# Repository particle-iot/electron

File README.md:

# Electron

The Electron is a tiny cellular development kit based around U-Blox's SARA U-series (3G) or G-series (2G) cellular modem module and a STM32F205 ARM Cortex M3 microcontroller.

The Electron has a footprint which is a drop-in compatible with the Particle Photon or Core.

Compared to the Particle Photon, the Electron introduces additional hardware features and changes:

1. JST LiPo battery connector.
2. Switch-mode battery charge management and system power path management circuit.
3. Fuel gauge circuit for lithium batteries.
4. Nano-SIM connector.
5. Access to USB data lines. 
6. 12 additional GPIO Pins.
7. 4 additional ADC channels.
8. 6 Timer channels exposed.
9. 2 additional UART peripherals.
10. 1 additional SPI and CAN peripheral.

A detailed description of the pin mapping can be found in **electron-pinmap_v1** spreadsheet.
* Sheet 1: Overview of the Electron pin-out.
* Sheet 2: Overview of the Photon pin-out for comparison.

### Pin Descriptions:
- **VIN:** This is the power supply pin to the Electron with a voltage range of 3.6 to 5.5VDC (internally regulated down to 3.3VDC). When the Electron is powered via its USB port, this pin will *ouput* a voltage of approximately 4.7VDC. Why 4.7 and not 5? Well, the actual voltage will be the USB voltage, which is normally 5, minus the forward voltage drop (0.3V) of the protection diode.
- **RST:** This is an active-low reset pin for the Electron.
- **VBAT:** Supply to the internal RTC, backup registers and SRAM (1.8 to 3.3VDC).
- **3V3:** This pin is the output of the on-board regulator. When powering the Photon via VIN or the USB port, this pin will *output* a voltage of 3.3VDC.
- **WKP:** This is an active-high input that allows you to wakeup the module from sleep/deep sleep modes. When not used as a WAKEUP, this pin can also be used as a digital GPIO, ADC input or PWM.
- **A0 - A5:** These can be used as digital GPIOs, ADC inputs. Alternate functions include: SPI, PWM and DAC.
- **B0 - B5:** These can be used as digital GPIOs, partial ADC inputs, partial PWM outputs.
- **C0 - C5:** These can be used as digital GPIOs.
- **D0 - D7:** These can be used as digital GPIOs. Alternate functions include: UART, SPI, I2C, PWM and CAN. 
- **DAC:** This pin can be used as a digital GPIO, ADC input or as a DAC ouput.
- **RX:** Primarily used as UART RX, but can also be used as a digital GPIO, ADC input or PWM.
- **TX:** Primarily used as UART TX, but can also be used as a digital GPIO, ADC input or PWM.

Please review the pinmap spreadsheet to better understand the alternate functions of the GPIO pins.

### Eagle (schematic, pcb layout and drc):
**eagle** contains the history of Electron designs and **electron_v020** is the latest design.  The **libraries** folder contains the Eagle library for parts used on the Electron.

### License

Designed by Particle. Distributed under a Creative Commons Attribution, Share-Alike license.
Development kits based on this product should be distributed under a similar license.
Commercial products using the Electron as a reference design need not comply with this license; further questions can be sent to hello@particle.io.
Check license.txt for more information.

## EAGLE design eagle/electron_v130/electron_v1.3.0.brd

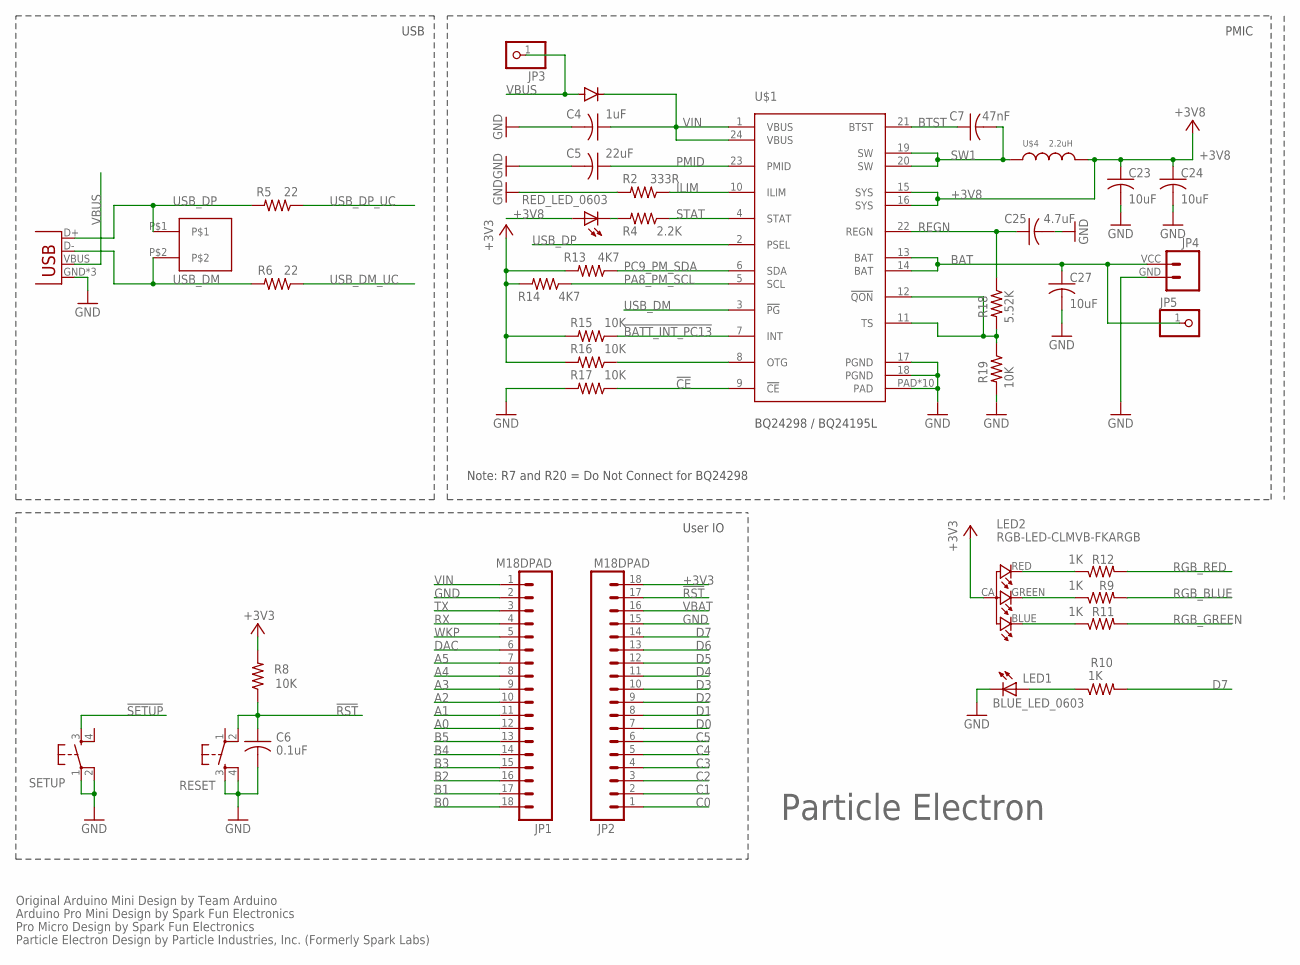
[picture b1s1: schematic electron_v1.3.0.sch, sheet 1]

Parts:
BLUE_LED_0603: LEDNOSILK; LED-0603-NS
C4: 1uF; C0603_B
C5: 22uF; C0603_B
C6: 0.1uF; C0402_B
C7: 47nF; C0402_B
C23, C24, C27: 10uF; C0603_B
C25: 4.7uF; C0603_B
JP1, JP2: M18DPAD; 1X18-D-PADS
JP3, JP5: PINHD-1X1NOSILK; 1X01_NO_SILK
JP4: M024UCON-15767; JST-2-SMD-VERT
LED2: RGB-LED-CLMVB-FKARGB; PLCC4-2MM-RGB
R2: 333R; R0402_B
R4: 2.2K; R0402_B
R5, R6: 22; R0402_B
R8, R15, R16, R17, R19: 10K; R0402_B
R9, R10, R11, R12: 1K; R0402_B
R13, R14: 4K7; R0402_B
R18: 5.52K; R0402_B
RED_LED_0603: LED0603; LED-0603
RESET: KMR211GLFS; TACTILE_SWITCH_SMD
SETUP: KMR211GLFS; TACTILE_SWITCH_SMD
U$1: BQ24298 / BQ24195L; QFN24
U$3: DIODE_NT; DIODE-DO-220AA_NT(SMP)
U$4: 2.2uH; INDUCTOR-4040
U$7: M02_0.05_HEADER
X1: USB-MICROB; USB-MICROB-SLOT-HOLE

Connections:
!BATT_INT_PC13: R15.1, U$1.7 (INT); also elsewhere on the board
!CE: R17.1, U$1.9 (!CE)
!RST: C6.1, JP2.17, R8.1, RESET.2; also elsewhere on the board
!SETUP: SETUP.3; also elsewhere on the board
+3V3: JP2.18, LED2.CA (1), R8.2, R13.2, R14.2, R15.2, R16.2; also elsewhere on the board
+3V8: C23.1, C24.1, RED_LED_0603.A, U$1.15 (SYS), U$1.16 (SYS), U$4.P$2 (2); also elsewhere on the board
A0: JP1.12; also elsewhere on the board
A1: JP1.11; also elsewhere on the board
A2: JP1.10; also elsewhere on the board
A3: JP1.9; also elsewhere on the board
A4: JP1.8; also elsewhere on the board
A5: JP1.7; also elsewhere on the board
B0: JP1.18; also elsewhere on the board
B1: JP1.17; also elsewhere on the board
B2: JP1.16; also elsewhere on the board
B3: JP1.15; also elsewhere on the board
B4: JP1.14; also elsewhere on the board
B5: JP1.13; also elsewhere on the board
BAT: C27.1, JP4.VCC (2), JP5.1, U$1.13 (BAT), U$1.14 (BAT); also elsewhere on the board
BTST: C7.1, U$1.21 (BTST)
C0: JP2.1; also elsewhere on the board
C1: JP2.2; also elsewhere on the board
C2: JP2.3; also elsewhere on the board
C3: JP2.4; also elsewhere on the board
C4: JP2.5; also elsewhere on the board
C5: JP2.6; also elsewhere on the board
D0: JP2.7; also elsewhere on the board
D1: JP2.8; also elsewhere on the board
D2: JP2.9; also elsewhere on the board
D3: JP2.10; also elsewhere on the board
D4: JP2.11; also elsewhere on the board
D5: JP2.12; also elsewhere on the board
D6: JP2.13; also elsewhere on the board
D7: JP2.14, R10.2; also elsewhere on the board
DAC: JP1.6; also elsewhere on the board
GND: BLUE_LED_0603.C, C4.2, C5.2, C6.2, C23.2, C24.2, C25.2, C27.2, JP1.2, JP2.15, JP4.GND (1), R2.2, R17.2, R19.2, RESET.3, RESET.4, SETUP.1, SETUP.2, U$1.17 (PGND), U$1.18 (PGND), U$1.PAD, U$1.PAD@1 (PAD), U$1.PAD@2 (PAD), U$1.PAD@3 (PAD), U$1.PAD@4 (PAD), U$1.PAD@5 (PAD), U$1.PAD@6 (PAD), U$1.PAD@7 (PAD), U$1.PAD@8 (PAD), U$1.PAD@9 (PAD), X1.GND, X1.MT1 (GND), X1.MT2 (GND); also elsewhere on the board
ILIM: R2.1, U$1.10 (ILIM)
LED1: BLUE_LED_0603.A, R10.1
unnamed: R4.2, RED_LED_0603.C
unnamed: R16.1, U$1.8 (OTG)
unnamed: LED2.BLUE (2), R11.1
unnamed: LED2.GREEN (3), R9.1
unnamed: LED2.RED (4), R12.1
PA8_PM_SCL: R14.1, U$1.5 (SCL); also elsewhere on the board
PC9_PM_SDA: R13.1, U$1.6 (SDA); also elsewhere on the board
PMID: C5.1, U$1.23 (PMID)
REGN: C25.1, R18.1, U$1.22 (REGN)
RGB_BLUE: R11.2; also elsewhere on the board
RGB_GREEN: R9.2; also elsewhere on the board
RGB_RED: R12.2; also elsewhere on the board
RX: JP1.4; also elsewhere on the board
STAT: R4.1, U$1.4 (STAT)
SW1: C7.2, U$1.19 (SW), U$1.20 (SW), U$4.P$1 (1)
TS: R18.2, R19.1, U$1.11 (TS), U$1.12 (!QON)
TX: JP1.3; also elsewhere on the board
USB_DM: R6.2, U$1.3 (!PG), U$7.P$2, X1.D-
USB_DM_UC: R6.1; also elsewhere on the board
USB_DP: R5.2, U$1.2 (PSEL), U$7.P$1, X1.D+
USB_DP_UC: R5.1; also elsewhere on the board
VBAT: JP2.16; also elsewhere on the board
VBUS: JP3.1, U$3.ANODE, X1.VBUS
VIN: C4.1, JP1.1, U$1.1 (VBUS), U$1.24 (VBUS), U$3.CATHODE
WKP: JP1.5; also elsewhere on the board

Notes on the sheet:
PMIC
User IO
USB
Particle Electron
Note: R7 and R20 = Do Not Connect for BQ24298
Original Arduino Mini Design by Team Arduino
Arduino Pro Mini Design by Spark Fun Electronics
Pro Micro Design by Spark Fun Electronics
Particle Electron Design by Particle Industries, Inc. (Formerly Spark Labs)

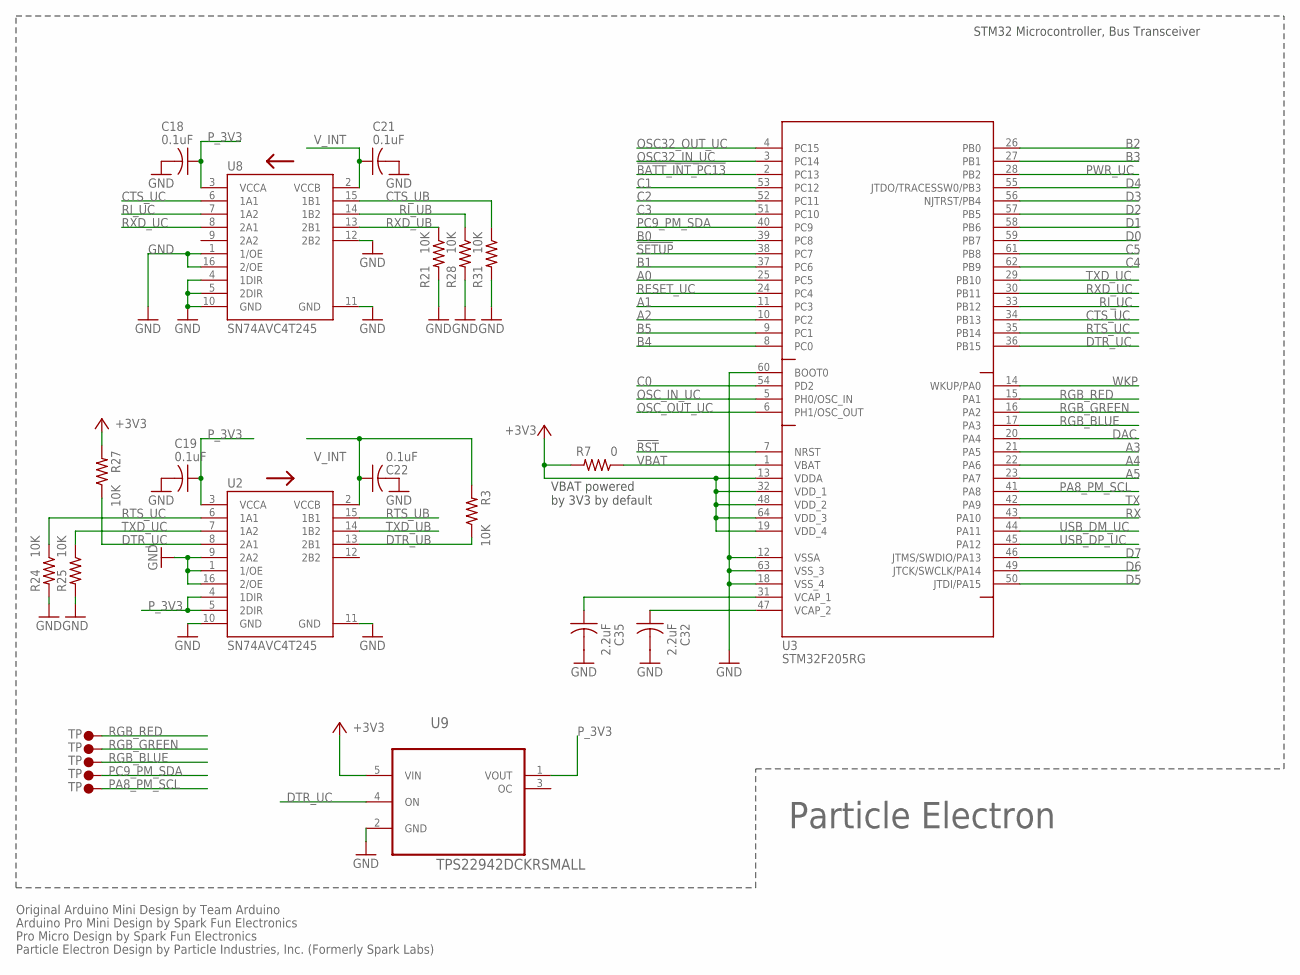
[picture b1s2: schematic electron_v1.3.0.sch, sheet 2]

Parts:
C18, C19, C21, C22: 0.1uF; C0402_B
C32, C35: 2.2uF; C0402_B
R3, R21, R24, R25, R27, R28, R31: 10K; R0402_B
R7: 0; R0402_B
U2, U8: SN74AVC4T245; UFQFN-16
U3: STM32F205RG; LQFP64
U9: TPS22942DCKRSMALL; SC70-5
U$8, U$9, U$11, U$12, U$13: TP0; TP30_BOT

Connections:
!BATT_INT_PC13: U3.2 (PC13); also elsewhere on the board
!RST: U3.7 (NRST); also elsewhere on the board
!SETUP: U3.38 (PC7); also elsewhere on the board
+3V3: R7.2, R27.2, U3.13 (VDDA), U3.19 (VDD_4), U3.32 (VDD_1), U3.48 (VDD_2), U3.64 (VDD_3), U9.5 (VIN); also elsewhere on the board
A0: U3.25 (PC5); also elsewhere on the board
A1: U3.11 (PC3); also elsewhere on the board
A2: U3.10 (PC2); also elsewhere on the board
A3: U3.21 (PA5); also elsewhere on the board
A4: U3.22 (PA6); also elsewhere on the board
A5: U3.23 (PA7); also elsewhere on the board
B0: U3.39 (PC8); also elsewhere on the board
B1: U3.37 (PC6); also elsewhere on the board
B2: U3.26 (PB0); also elsewhere on the board
B3: U3.27 (PB1); also elsewhere on the board
B4: U3.8 (PC0); also elsewhere on the board
B5: U3.9 (PC1); also elsewhere on the board
C0: U3.54 (PD2); also elsewhere on the board
C1: U3.53 (PC12); also elsewhere on the board
C2: U3.52 (PC11); also elsewhere on the board
C3: U3.51 (PC10); also elsewhere on the board
C4: U3.62 (PB9); also elsewhere on the board
C5: U3.61 (PB8); also elsewhere on the board
CTS_UB: R31.1, U8.15 (1B1); also elsewhere on the board
CTS_UC: U3.34 (PB13), U8.6 (1A1)
D0: U3.59 (PB7); also elsewhere on the board
D1: U3.58 (PB6); also elsewhere on the board
D2: U3.57 (PB5); also elsewhere on the board
D3: U3.56 (NJTRST/PB4); also elsewhere on the board
D4: U3.55 (JTDO/TRACESSW0/PB3); also elsewhere on the board
D5: U3.50 (JTDI/PA15); also elsewhere on the board
D6: U3.49 (JTCK/SWCLK/PA14); also elsewhere on the board
D7: U3.46 (JTMS/SWDIO/PA13); also elsewhere on the board
DAC: U3.20 (PA4); also elsewhere on the board
DTR_UB: R3.1, U2.13 (2B1); also elsewhere on the board
DTR_UC: R27.1, U2.8 (2A1), U3.36 (PB15), U9.4 (ON)
GND: C18.2, C19.2, C21.2, C22.2, C32.2, C35.2, R21.2, R24.2, R25.2, R28.2, R31.2, U2.1 (1/OE), U2.9 (2A2), U2.10 (GND), U2.11 (GND), U2.16 (2/OE), U3.12 (VSSA), U3.18 (VSS_4), U3.60 (BOOT0), U3.63 (VSS_3), U8.1 (1/OE), U8.4 (1DIR), U8.5 (2DIR), U8.10 (GND), U8.11 (GND), U8.12 (2B2), U8.16 (2/OE), U9.2 (GND); also elsewhere on the board
unnamed: C35.1, U3.31 (VCAP_1)
unnamed: C32.1, U3.47 (VCAP_2)
OSC32_IN_UC: U3.3 (PC14); also elsewhere on the board
OSC32_OUT_UC: U3.4 (PC15); also elsewhere on the board
OSC_IN_UC: U3.5 (PH0/OSC_IN); also elsewhere on the board
OSC_OUT_UC: U3.6 (PH1/OSC_OUT); also elsewhere on the board
PA8_PM_SCL: U3.41 (PA8), U$9.P$1; also elsewhere on the board
PC9_PM_SDA: U3.40 (PC9), U$8.P$1; also elsewhere on the board
PWR_UC: U3.28 (PB2); also elsewhere on the board
P_3V3: C18.1, C19.1, U2.3 (VCCA), U2.4 (1DIR), U2.5 (2DIR), U8.3 (VCCA), U9.1 (VOUT)
RESET_UC: U3.24 (PC4); also elsewhere on the board
RGB_BLUE: U3.17 (PA3), U$13.P$1; also elsewhere on the board
RGB_GREEN: U3.16 (PA2), U$12.P$1; also elsewhere on the board
RGB_RED: U3.15 (PA1), U$11.P$1; also elsewhere on the board
RI_UB: R28.1, U8.14 (1B2); also elsewhere on the board
RI_UC: U3.33 (PB12), U8.7 (1A2)
RTS_UB: U2.15 (1B1); also elsewhere on the board
RTS_UC: R24.1, U2.6 (1A1), U3.35 (PB14)
RX: U3.43 (PA10); also elsewhere on the board
RXD_UB: R21.1, U8.13 (2B1); also elsewhere on the board
RXD_UC: U3.30 (PB11), U8.8 (2A1)
TX: U3.42 (PA9); also elsewhere on the board
TXD_UB: U2.14 (1B2); also elsewhere on the board
TXD_UC: R25.1, U2.7 (1A2), U3.29 (PB10)
USB_DM_UC: U3.44 (PA11); also elsewhere on the board
USB_DP_UC: U3.45 (PA12); also elsewhere on the board
VBAT: R7.1, U3.1 (VBAT); also elsewhere on the board
V_INT: C21.1, C22.1, R3.2, U2.2 (VCCB), U8.2 (VCCB); also elsewhere on the board
WKP: U3.14 (WKUP/PA0); also elsewhere on the board

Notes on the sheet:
Particle Electron
STM32 Microcontroller, Bus Transceiver
Original Arduino Mini Design by Team Arduino
Arduino Pro Mini Design by Spark Fun Electronics
Pro Micro Design by Spark Fun Electronics
Particle Electron Design by Particle Industries, Inc. (Formerly Spark Labs)
VBAT powered by 3V3 by default

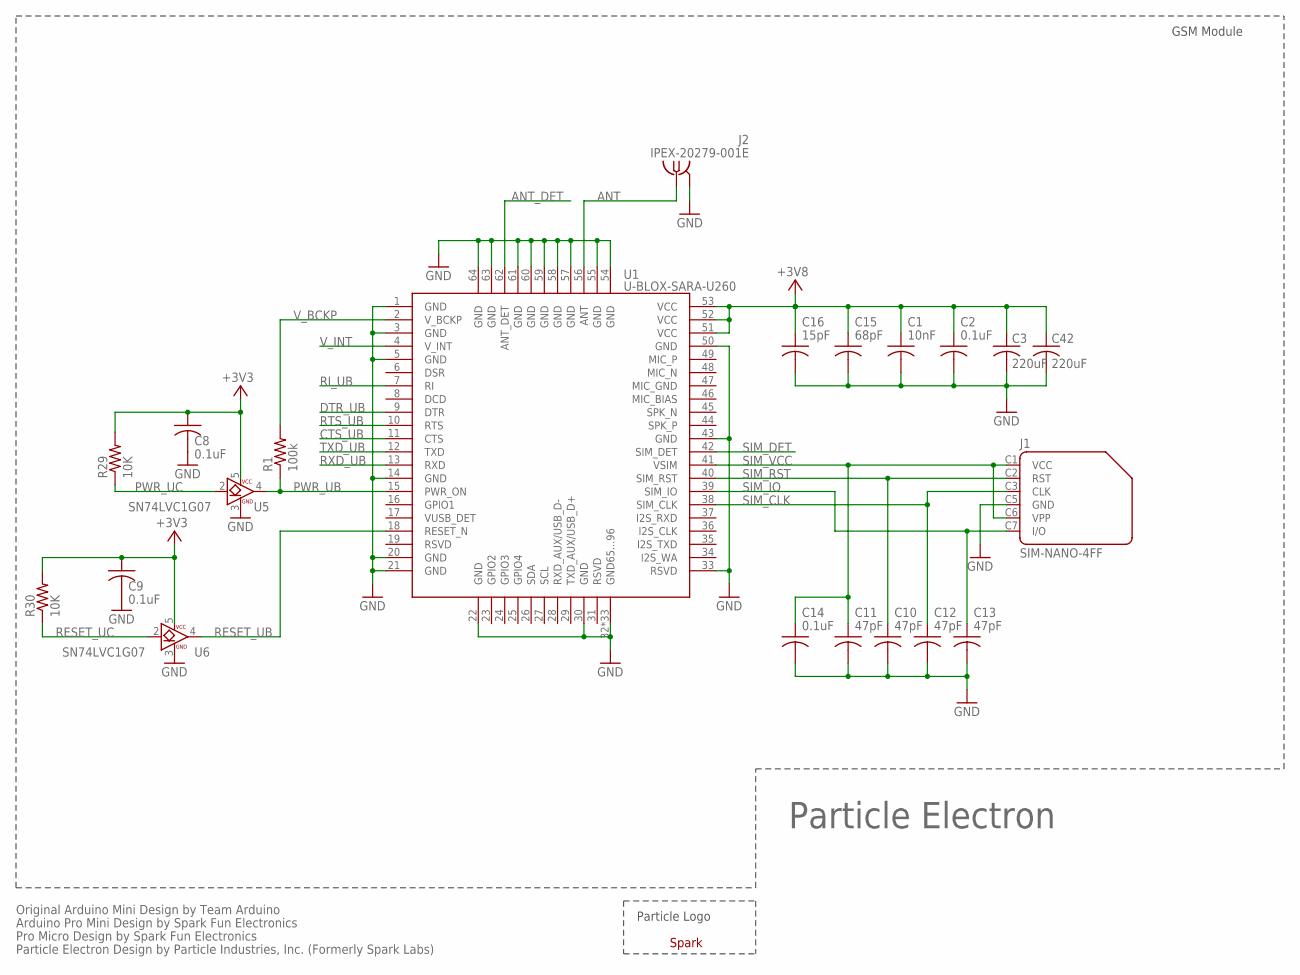
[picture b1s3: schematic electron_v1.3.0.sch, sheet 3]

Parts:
C1: 10nF; C0402_B
C2, C8, C9, C14: 0.1uF; C0402_B
C3, C42: 220uF; C1210
C10, C11, C12, C13: 47pF; C0402_B
C15: 68pF; C0402_B
C16: 15pF; C0402_B
J1: SIM-NANO-4FF; GCT-SIM8100
J2: IPEX-20279-001E
R1: 100k; R0402_B
R29, R30: 10K; R0402_B
U1: U-BLOX-SARA-U260; U-BLOX-SARA-U2
U5, U6: SN74LVC1G07; SC-70-5
U$2: SPARK_LOGO2

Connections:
+3V3: C8.1, C9.1, R29.2, R30.2, U5.5 (VCC), U6.5 (VCC); also elsewhere on the board
+3V8: C1.1, C2.1, C3.1, C15.1, C16.1, C42.1, U1.51 (VCC), U1.52 (VCC), U1.53 (VCC); also elsewhere on the board
ANT: J2.1, U1.56 (ANT)
ANT_DET: U1.62 (ANT_DET)
CTS_UB: U1.11 (CTS); also elsewhere on the board
DTR_UB: U1.9 (DTR); also elsewhere on the board
GND: C1.2, C2.2, C3.2, C8.2, C9.2, C10.2, C11.2, C12.2, C13.2, C14.2, C15.2, C16.2, C42.2, J1.C5 (GND), J2.2@1 (GND), J2.2@2 (GND), U1.1 (GND), U1.3 (GND), U1.5 (GND), U1.14 (GND), U1.20 (GND), U1.21 (GND), U1.22 (GND), U1.30 (GND), U1.32 (GND65...96), U1.33 (RSVD), U1.43 (GND), U1.50 (GND), U1.54 (GND), U1.55 (GND), U1.57 (GND), U1.58 (GND), U1.59 (GND), U1.60 (GND), U1.61 (GND), U1.63 (GND), U1.64 (GND), U1.65 (GND65...96), U1.66 (GND65...96), U1.67 (GND65...96), U1.68 (GND65...96), U1.69 (GND65...96), U1.70 (GND65...96), U1.71 (GND65...96), U1.72 (GND65...96), U1.73 (GND65...96), U1.74 (GND65...96), U1.75 (GND65...96), U1.76 (GND65...96), U1.77 (GND65...96), U1.78 (GND65...96), U1.79 (GND65...96), U1.80 (GND65...96), U1.81 (GND65...96), U1.82 (GND65...96), U1.83 (GND65...96), U1.84 (GND65...96), U1.85 (GND65...96), U1.86 (GND65...96), U1.87 (GND65...96), U1.88 (GND65...96), U1.89 (GND65...96), U1.90 (GND65...96), U1.91 (GND65...96), U1.92 (GND65...96), U1.93 (GND65...96), U1.94 (GND65...96), U1.95 (GND65...96), U1.96 (GND65...96), U5.3 (GND), U6.3 (GND); also elsewhere on the board
PWR_UB: R1.1, U1.15 (PWR_ON), U5.4 (B)
PWR_UC: R29.1, U5.2 (A); also elsewhere on the board
RESET_UB: U1.18 (RESET_N), U6.4 (B)
RESET_UC: R30.1, U6.2 (A); also elsewhere on the board
RI_UB: U1.7 (RI); also elsewhere on the board
RTS_UB: U1.10 (RTS); also elsewhere on the board
RXD_UB: U1.13 (RXD); also elsewhere on the board
SIM_CLK: C12.1, J1.C3 (CLK), U1.38 (SIM_CLK)
SIM_DET: U1.42 (SIM_DET)
SIM_IO: C13.1, J1.C7 (I/O), U1.39 (SIM_IO)
SIM_RST: C10.1, J1.C2 (RST), U1.40 (SIM_RST)
SIM_VCC: C11.1, C14.1, J1.C1 (VCC), J1.C6 (VPP), U1.41 (VSIM)
TXD_UB: U1.12 (TXD); also elsewhere on the board
V_BCKP: R1.2, U1.2 (V_BCKP)
V_INT: U1.4 (V_INT); also elsewhere on the board

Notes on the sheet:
Particle Electron
GSM Module
Particle Logo
Original Arduino Mini Design by Team Arduino
Arduino Pro Mini Design by Spark Fun Electronics
Pro Micro Design by Spark Fun Electronics
Particle Electron Design by Particle Industries, Inc. (Formerly Spark Labs)

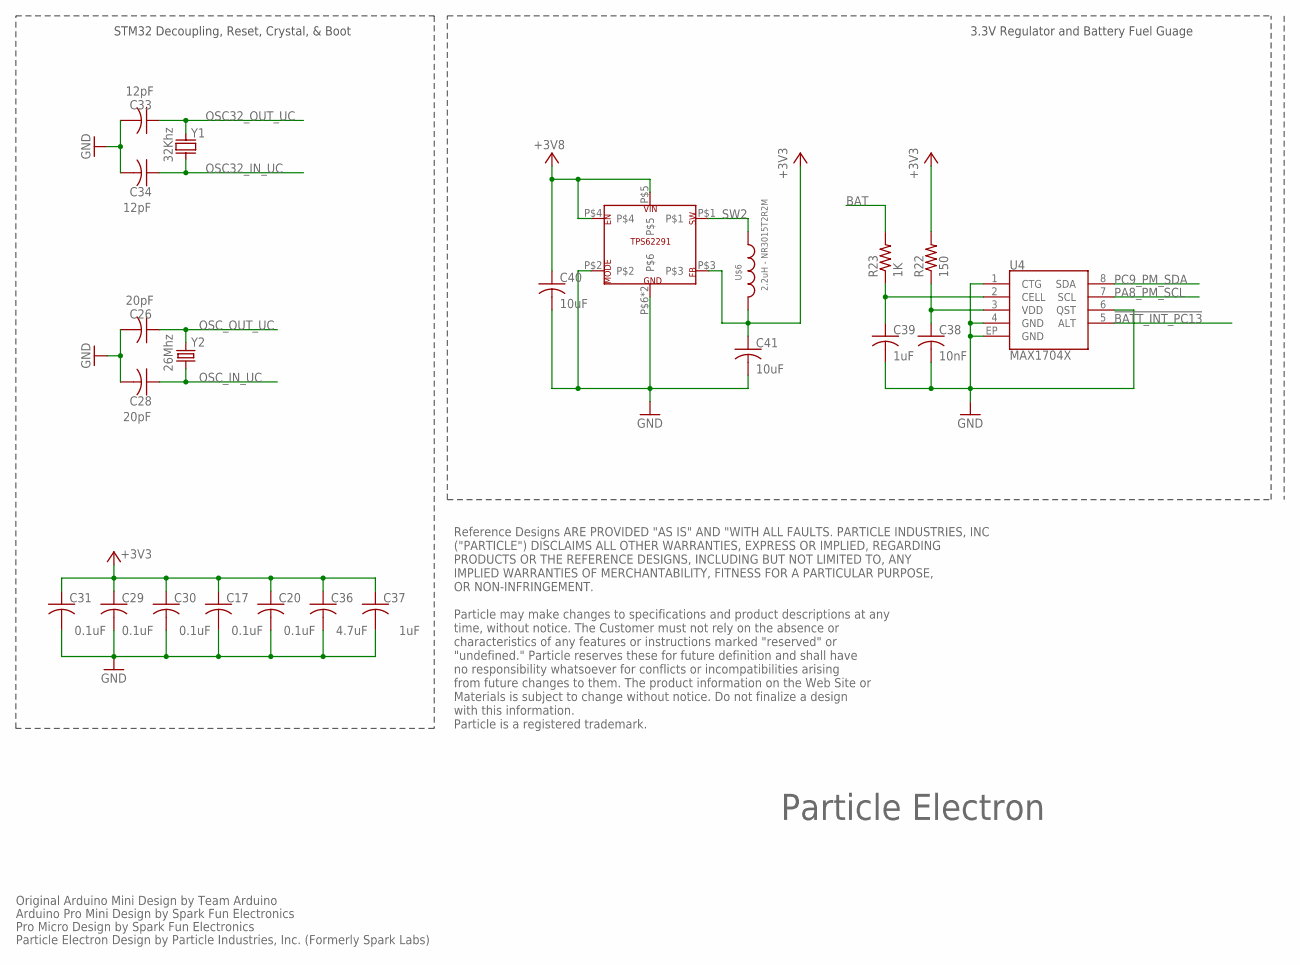
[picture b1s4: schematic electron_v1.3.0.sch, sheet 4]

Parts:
C17, C20, C29, C30, C31: 0.1uF; C0402_B
C26, C28: 20pF; C0402_B
C33, C34: 12pF; C0402_B
C36: 4.7uF; C0402_B
C37, C39: 1uF; C0402_B
C38: 10nF; C0402_B
C40, C41: 10uF; C0603_B
R22: 150; 0603-RES
R23: 1K; 0603-RES
U4: MAX1704X; TDFN-8
U$5: TPS62291DRV; S-PWSON-N6
U$6: 2.2uH - NR3015T2R2M; INDUCTOR-NR3015
Y1: 32Khz; FC135
Y2: 26Mhz; CRYSTAL-SMD-5X3

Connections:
!BATT_INT_PC13: U4.5 (ALT); also elsewhere on the board
+3V3: C17.1, C20.1, C29.1, C30.1, C31.1, C36.1, C37.1, C41.1, R22.2, U$5.P$3, U$6.2; also elsewhere on the board
+3V8: C40.1, U$5.P$4, U$5.P$5; also elsewhere on the board
BAT: R23.2; also elsewhere on the board
GND: C17.2, C20.2, C26.2, C28.2, C29.2, C30.2, C31.2, C33.2, C34.2, C36.2, C37.2, C38.2, C39.2, C40.2, C41.2, U4.1 (CTG), U4.4 (GND), U4.6 (QST), U4.EP (GND), U$5.P$2, U$5.P$6, U$5.TP; also elsewhere on the board
unnamed: C39.1, R23.1, U4.2 (CELL)
unnamed: C38.1, R22.1, U4.3 (VDD)
OSC32_IN_UC: C34.1, Y1.X1 (1); also elsewhere on the board
OSC32_OUT_UC: C33.1, Y1.X2 (2); also elsewhere on the board
OSC_IN_UC: C28.1, Y2.1; also elsewhere on the board
OSC_OUT_UC: C26.1, Y2.3 (2); also elsewhere on the board
PA8_PM_SCL: U4.7 (SCL); also elsewhere on the board
PC9_PM_SDA: U4.8 (SDA); also elsewhere on the board
SW2: U$5.P$1, U$6.1

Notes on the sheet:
Particle Electron
STM32 Decoupling, Reset, Crystal, & Boot
3.3V Regulator and Battery Fuel Guage
Original Arduino Mini Design by Team Arduino
Arduino Pro Mini Design by Spark Fun Electronics
Pro Micro Design by Spark Fun Electronics
Particle Electron Design by Particle Industries, Inc. (Formerly Spark Labs)
Reference Designs ARE PROVIDED "AS IS" AND "WITH ALL FAULTS. PARTICLE INDUSTRIES, INC ("PARTICLE") DISCLAIMS ALL OTHER WARRANTIES, EXPRESS OR IMPLIED, REGARDING PRODUCTS OR THE REFERENCE DESIGNS, INCLUDING BUT NOT LIMITED TO, ANY IMPLIED WARRANTIES OF MERCHANTABILITY, FITNESS FOR A PARTICULAR PURPO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

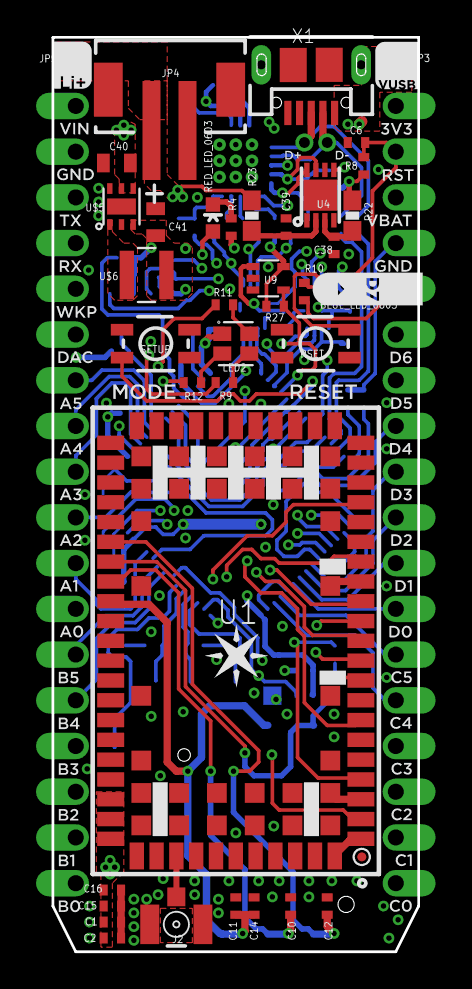
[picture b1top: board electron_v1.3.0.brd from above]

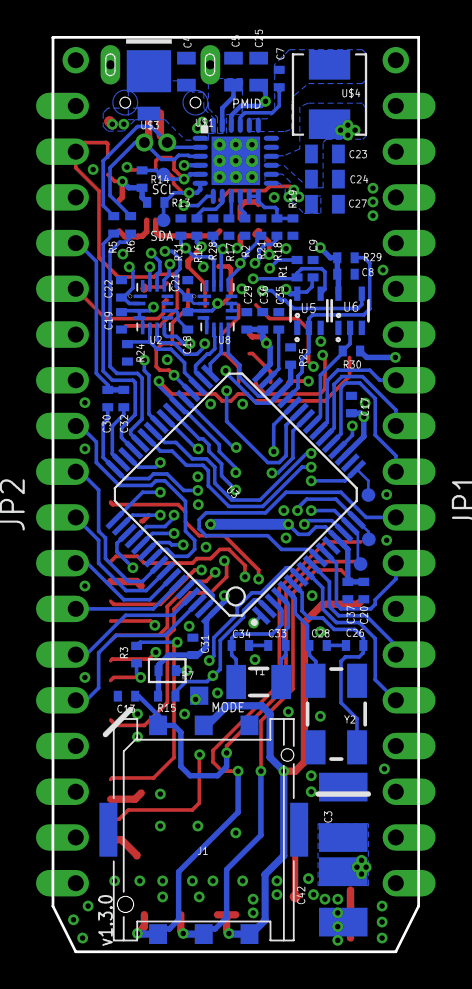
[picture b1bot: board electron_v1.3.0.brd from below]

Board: 4 copper layers, 20.3 x 50.8 mm, 106 parts (62 on the bottom side), 96 nets.

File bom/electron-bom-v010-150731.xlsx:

| NAME | PARTICLE ELECTRON
 | IDENTIFIER | DESCRIPTION | VALUE | V | A | W | TOL | PACKAGE ID | DESIGNATOR | QTY | MANUFACTURER | MANUFACTURER P/N
 | ACCESSORY | Mini Breadboard, White, 400pt tie point, 3.5 x 4.5cm |  |  |  |  |  | 3.5 x 4.5cm | ACC1 | 1 | Ningbo Everest | N/A
 | ACCESSORY | USB Micro-B Cable, 0.5m, White with Molded Logo |  |  |  |  |  | USB Micro-B, 0.5m | ACC2 | 1 | HOP Electronics | N/A
 | ACCESSORY | Li-Po Battery with JST Connector (2.0mm spacing, 2 pin), 3.7V, 2000mAh |  |  |  |  |  | 51mm x 34mm x 11.3mm | BAT1 | 1 | PKCell | LIPO 103450 2000mAh 3.7V
 | ANTENNA | Antenna - Penta band 850/900/1800/1900/2100 MHz |  |  |  |  |  | IPEX MHFI (U.FL) | ANT1 | 1 | Taoglas Taoglas Fei Yu Xin | PC104.07.0165C FXP14.07.0100A IPEX-PCB-113-L42
 | CAPACITOR | Ceramic Capacitor | 0.1uF | 6.3V |  |  | 0.1 | 0402 | C14, C17, C18, C19, C2, C20, C21, C22, C29, C30, C31, C6, C8, C9 | 14
 | CAPACITOR | Ceramic Capacitor | 10nF | 6.3V |  |  | 0.1 | 0402 | C1, C38 | 2
 | CAPACITOR | Ceramic Capacitor, X5R, Low ESR (<70 mΩ) | 10uF | 6.3V |  |  | 0.1 | 0603 | C23, C24, C27 | 3
 | CAPACITOR | Ceramic Capacitor | 12pF | 6.3V |  |  | 0.1 | 0402 | C33, C34 | 2
 | CAPACITOR | Ceramic Capacitor | 15pF | 6.3V |  |  | 0.1 | 0402 | C16 | 1
 | CAPACITOR | Ceramic Capacitor | 1uF | 6.3V |  |  | 0.1 | 0402 | C37, C39 | 3
 | CAPACITOR | Ceramic Capacitor, X5R, Low ESR (<70 mΩ) | 1uF | ≥25V |  |  | 0.1 | 0603 | C4 | 3
 | CAPACITOR | Ceramic Capacitor, X5R, Low ESR (<70 mΩ) | 2.2uF | 6.3V |  |  | 0.1 | 0402 | C32, C35 | 4
 | CAPACITOR | Ceramic Capacitor, X5R, Low ESR (<70 mΩ) | 2.2uF | 6.3V |  |  | 0.1 | 0603 | C40, C41 | 4
 | CAPACITOR | Ceramic Capacitor | 20pF | 6.3V |  |  | 0.1 | 0402 | C26, C28 | 2
 | CAPACITOR | Ceramic Capacitor, X5R, Low ESR (<70 mΩ) | 20uF | 6.3V |  |  | 0.1 | 0603 | C5 | 1
 | CAPACITOR | Tantalum Capacitor | 220uF | 6.3V |  |  | 0.1 | 2312 (6032 metric) | C3 | 1
 | CAPACITOR | Ceramic Capacitor, X5R, Low ESR (<70 mΩ) | 4.7uF | 6.3V |  |  | 0.1 | 0402 | C36 | 2
 | CAPACITOR | Ceramic Capacitor, X5R, Low ESR (<70 mΩ) | 4.7uF | 6.3V |  |  | 0.1 | 0603 | C25 | 2
 | CAPACITOR | Ceramic Capacitor | 47nF | 6.3V |  |  | 0.1 | 0402 | C7 | 1
 | CAPACITOR | Ceramic Capacitor | 47pF | 6.3V |  |  | 0.1 | 0402 | C10, C11, C12, C13 | 4
 | CAPACITOR | Ceramic Capacitor | 68pF | 6.3V |  |  | 0.1 | 0402 | C15 | 1
 | CONNECTOR | JST Connector | 2-pin |  |  |  |  | SMD, 2-pin, Vertical | JP4 | 1 | Kaweei | CW2001-02G-M01-D
 | CONNECTOR | Male Header (0.05" pitch) x 2 pins | 1x2 |  |  |  |  | 1x2, 0.05" pitch | U$7 | 1 | Kaweei
 | CONNECTOR | Male Header (0.1" pitch) x 18 pins | 1x18 |  |  |  |  | 1x18, 0.1" pitch | JP1, JP2 | 2 | Kaweei
 | CONNECTOR | USB Micro Connector with Slots, SMD |  |  |  |  |  | USB-MICROB-SLOT-HOLE | X1 | 1 | Kaweei | CMCUSB-5BFM2G-01-D
 | CONNECTOR | uFL Connector, IPEX-20279-001E, SMD |  |  |  |  |  | SMD | J2 | 1 | Kaweei | P1163-0140R
 | CONNECTOR | Nano SIM Card Slot |  |  |  |  |  | 10mm x 12.3mm | J1 | 1 | Kaweei | CSIM2545-06S-X
 | CRYSTAL | 26MHz, 18pF Load Capacitance, SMD5032, 4 pad | 26MHz |  |  |  | <±20ppm | 4-SMD, 5.0 x 3.2mm | Y2 | 1 | Song Ji | SJSMD5026M00018F20
 | CRYSTAL | 32.768KHz, 12.5pF Load Capacitance, SMD3215, 2 pad | 32.768KHz |  |  |  | <±20ppm | 2-SMD, 1.5 x 3.2mm | Y1 | 1 | Song Ji | SJ FC1332K012F520P
 | DIODE | Schottky Diode |  | 30V | 3A |  |  | DO-220AA | U$3 | 1 | Vishay | SS3P3-M3/84A
 | IC | Buffer |  |  |  |  |  | SC-70-5 | U5, U6 | 2 | Texas Instruments | SN74LVC1G07DCKR
 | IC | IC 2-Wire Fuel Gauge |  |  |  |  |  | TDFN-8 | U4 | 1 | Maxim | MAX17043G+T
 | IC | GSM Module |  |  |  |  |  | 16 x 26 x 3mm | U1 | 1 | u-blox | SARA-G350 SARA-U260 SARA-U270
 | IC | IC Bus Transceiver |  |  |  |  |  | 16-UQFN | U2, U8 | 2 | Texas Instruments | SN74AVC4T245RSVR
 | IC | Microcontroller |  |  |  |  |  | LQFP64 | U3 | 1 | ST Microelectronics | STM32F205RGT6TR
 | IC | Power Management IC (PMIC) |  |  |  |  |  | 24VQFN | U$1 | 1 | Texas Instruments | BQ24195RGER
 | IC | Voltage Regulator |  |  |  |  |  | 6-DSGBA | U$5 | 1 | Texas Instruments | LM3281YFQR
 | INDUCTOR | Ferrite Core Power Inductor (for 3V3 Regulator) | 0.47uH |  | 2.65A 2A |  |  | 2.5mm x 2.0mm 2.0mm x 2.0mm | U$6 | 1 | Abracon (preferred) TDK (backup) | ASPI-2510-R47N-T2 VLS2012ET-R47N
 | INDUCTOR | Power Inductor (for PMIC) | 2.2uH |  | 5A 3.7A |  |  | 5.0mm x 5.0mm x 4.5mm 4.9mm x 4.9mm x 4.1mm | U$4 | 1 | TDK (preferred) Taiyo Yuden (backup) | VLC5045T-2R2N NRS5040T2R2NMGJV
 | LED | Blue, SMD | Blue |  |  |  |  | 0603 | LED1 | 1 | Everlight | 19-217/BHC-ZL1M2RY/3T
 | LED | Red, SMD | Red |  |  |  |  | 0603 | LED3 | 1 | Everlight | 19-217/R6C-AL1M2VY/3T
 | LED | LED RGB, SMD | RGB |  |  |  |  | 4-PLCC (3.2 mm x 2.8mm) | LED2 | 1 | Cree | CLMVB-FKA-CFHEHLCBB7A363
 | PACKAGING | Static bag |  |  |  |  |  | TBD | PKG1 | 1
 | PACKAGING | Bubble bag |  |  |  |  |  | TBD | PKG2 | 1
 | PCB | FR4 4-Layer Photon PCB, 2-sided, matte black soldermask, cyan silkscreen |  |  |  |  |  | 20 mm x 50 mm | PCB1 | 1 | Truly
 | RESISTOR | Resistor | 0R |  |  | 1/10W | 0.05 | 0402 | R20, R7 | 2
 | RESISTOR | Resistor | 100k |  |  | 1/10W | 0.05 | 0402 | R1 | 1
 | RESISTOR | Resistor | 10K |  |  | 1/10W | 0.05 | 0402 | R13, R14, R15, R16, R17, R19, R8 | 7
 | RESISTOR | Resistor | 150R |  |  | 1/4W | 0.01 | 0603 | R22 | 1
 | RESISTOR | Resistor | 1K |  |  | 1/10W | 0.05 | 0603 | R23 | 1
 | RESISTOR | Resistor | 1K |  |  | 1/10W | 0.05 | 0402 | R10, R11, R12, R9 | 5
 | RESISTOR | Resistor | 2.2K |  |  | 1/10W | 0.05 | 0402 | R4 | 1
 | RESISTOR | Resistor | 22R |  |  | 1/10W | 0.01 | 0402 | R5, R6 | 2
 | RESISTOR | Resistor | 333R |  |  | 1/10W | 0.01 | 0402 | R2 | 1
 | RESISTOR | Resistor | 4K7 |  |  | 1/10W | 0.05 | 0402 | R21, R3 | 2
 | RESISTOR | Resistor | 5.52K |  |  | 1/10W | 0.01 | 0402 | R18 | 1
 | SIM | Nano SIM Card |  |  |  |  |  | Nano SIM | SIM1 | 1 | Telefonia | N/A
 | STICKER | UPC Sticker for the Electron |  |  |  |  |  | 40 mm x 20 mm | STK2 | 1 | Mei Ya | G350 (2G) - 724131462277 U260 (3G N.A.) - 724131462284 U270 (3G World) - 724131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
 | STICKER | "STICK-VINYL-2IN" sticker, 2", Circular, PVC - 5cm |  |  |  |  |  | Circular 2" | STK1 | 1 | Mei Ya
 | STICKER | Unique Barcode Sticker (DYMO 30346) |  |  |  |  |  | 1/2" x 1-7/8" | STK3 | 1 | Spark
 | SWITCH | Tactile Switch, Black Button | 160gF |  |  |  |  | 3.6mm x 3.1mm | MODE, RESET | 2 | Haoyu | TS-1185A-C

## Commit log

2015-07-29 Added 'Particle.lbr' Eagle Library
2015-07-29 Added .gitignore to ignore Eagle backup files
2015-07-29 Added Particle DRC and CAM files
2015-07-29 Added latest 'electron_v009' Eagle design folder/files (PCB Ver: 009)
2015-07-29 Added Manufacturing Gerber files for 'electron_v009'
2015-07-29 Added 'electron_v010' with improved RF layout & additional GND Vias
2015-07-29 updated readme wording
2015-07-29 Adding a BOM for v010
    Adding a BOM for the most current version of the Electron
2015-07-29 BOM tweaks v010
2015-07-29 BOM Tweaks again
2015-07-30 #8 Updated 3.3V regulator's inductor package footprint
2015-07-30 #7 Changed Button labels to SETUP and RESET
2015-07-30 #4 USB 5V exposed via hexagonal pad on top right corner above 3V3 pin
2015-07-30 #5 Added header pin labels that are not obscured by the u-blox module
2015-07-30 #1 Added u-blox positioning silkscreen
2015-07-30 Changed Particle IO to Particle
2015-07-30 added 18 pin header library part
2015-07-30 Added D pad footprint for Electron headers
    Device: M18
    Footprint: 1X18-D-PADS
2015-07-30 Added square long pad footprint for the Electron headers
    Device: M18
    Footprint: 1X18-SQR-LONG-PADS
2015-07-31 added 4020 type footprint to inductor device
    Device: Inductor
    Package: 4020TYPE
2015-07-31 #2 Replaced M18 round header pads with D-shaped pads and re-routed
2015-07-31 #10 ANT trace width @ RF net rules & deleted IPEX polygon cutouts
2015-07-31 #9 Added cutout on top layer under the ANT connector
2015-07-31 #13 Added more GND Vias around ANT connector and updated trace routes
2015-07-31 #11 Additional Vias added for battery trace connections
2015-07-31 Updated particle.lbr - Added a 4020 type inductor with bigger pads
2015-07-31 #12 Updated to bigger pads PMIC inductor footprint and power polygons
2015-07-31 Updated 5V header pad to round with drill size same as other headers
2015-07-31 Added more Vias on u-blox 3.8V trace connection (PCB Ver: 010 Ready)
2015-07-31 #15 Added Manufacturing Gerber files for 'electron_v010'
2015-07-31 Updated Top Silkscreen
2015-07-31 Updated Gerbers for PCB Ver 010
2015-07-31 added pin labels, thickened the text and moved particle logo
2015-07-31 generated new gerber files after adding pin labels
2015-07-31 Added specs for passives, some dottiest
    Check it out, yo
2015-08-01 Added some mfg documents for spinning up beta boards
    Added fab specs, 50 ohm impedance calcs, rf net PDF, and layer stackup
    explanation
2015-08-01 removed redundant gerber files
2015-08-03 Added electron_v010_schematic.pdf
2015-08-03 Added electron_v010_pcb-gerbers.pdf
2015-08-03 Updated Inductors in the BOM
    Hey Mohit!
2015-08-05 Added 'electron_v011' Eagle design folder/files (Work in Progress)
2015-08-05 BOM updated with passive values, some packaging stuff
    See the changelogzorzzzz :-)
2015-08-05 Manufacturing documents for the beta trials
2015-08-07 Updated BOM (C5 value from 20uF to 22uF)
2015-08-12 Updated BOM
    changed the quantity field of some passive components to match the
    correct number of designators.
2015-08-19 Added TPS62291 datasheet
2015-08-19 Created TPS62291DRV part in Particle library
2015-08-19 Replaced LM3281 with TPS62291 in schematic and updated circuit
2015-08-19 2.2uH inductor reused for 3.3V circuit, components placed and locked
2015-08-19 Completed v011 PCB routing for revised 3.3V power circuit #19
2015-08-19 Header pin labels updated #16
2015-08-19 Added orientation indicators to the silkscreen layers #17
2015-08-19 Added Manufacturing Gerber files for 'electron_v011'
2015-08-20 Updated BOM
    New voltage regulator, new power inductor, cross parts for passives.
2015-08-21 Added 'electron_v012' files-changed 3V3 power inductor footprint #21
2015-08-21 Minor silkscreen tweaks
2015-08-21 Added Manufacturing Gerber files for 'electron_v012'
2015-08-24 Updated Electron BOM
    removed extra part numbers from the antenna line
2015-08-25 Added PDF of 'electron_v012' schematic and pcb design
2015-08-27 added lipo and pmid 5v header
    change log:
    1. Exposed LiPo connection via a header
    2. Exposed PMID boost 5V via a header
    3. Lowered the 3V3 inductor and rotated its output cap to meet
    datasheet recommendations
2015-08-31 Updated Electron BOM
    Only includes Yageo/Samsung parts instead of Fenghua cross parts that
    did not meet spec.
2015-09-02 Updated BOM
    Moved battery part from separate SKU to same BOM as Electron
2015-09-03 Added Electron part!
    This one is for a dual row header with unpopulated PTH on the inside,
    like the Photon shields generally have.
2015-09-03 'electron_v013'
2015-09-03 Delete electron_v013.brd
    Delete this file because of my wrong operation
2015-09-03 Delete electron_v013.sch
    Delete this file because of my wrong operation
2015-09-03 Delete electron_v013_pcb.pdf
    Delete this file because of my wrong operation
2015-09-03 Delete electron_v013_sch.pdf
    Delete ti because of my wrong operation
2015-09-08 Updated BOM
    Updated BOM
2015-09-20 Missing fuel gauge datasheet
2015-09-22 Updated R18 resistor P/N
2015-10-26 updated bom to 151026 - resistor count changes
2015-10-26 Updated BOM with packaging changes
2015-11-02 updated BOM to v017-151102
    10K resistor qty from 12 to 13
    4K7 resistor qty from 3 to 2
    0R resistors deleted (3 to 0)
2015-11-02 Updated the changelog
2015-11-30 Pushing updated BOM so @mohitbhoite can make changes
    Hooray!
2015-11-30 updated BOM :page_with_curl: for dear Will Hart
2015-11-30 updated bom chnagelog column location
2015-12-08 Added SIM card sticker in 12/8 revision of the BOM
2015-12-14 added latest design files and updated dottiest
2015-12-14 added fuel gauge datasheet
2016-01-13 Updated BOM to include 0 ohm resistor
2016-01-14 added electron hardware data sheet graphics
2016-01-15 added schematic images
2016-04-06 added pdf of schematics and pcbs
2016-07-13 added new inductor footprint for cooper industries
2017-08-16 Fixes: 42
    https://github.com/spark/electron/issues/42
2019-05-27 Added hardware 1.3.0

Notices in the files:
parts and their libraries:
SparkFun-FreqCtrl: Licensing: CC v3.0 Share-Alike You are welcome to use this library for commercial purposes.
SparkFun-Connectors: Licensing: Creative Commons ShareAlike 4.0 International - https://creativecommons.org/licenses/by-sa/4.0
